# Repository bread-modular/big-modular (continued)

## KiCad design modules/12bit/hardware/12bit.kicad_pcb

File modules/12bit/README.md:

# 12bit — STM32G071 two-channel DAC voice (6HP)

modules/8bit moved from the ATtiny1616 to an **STM32G071C8T6**: its two 12-bit DAC channels
drive two outputs and the passive low-pass is gone (knob 3 is a plain knob). 6HP. (The S1
gate output was removed in S2. S3 adds a 3.0 V reference rail for the DACs, the ADC and the knobs.)

| Panel (top to bottom) | Circuit |
|---|---|
| **MIDI** in (TS) / **CV** in | 8bit MIDI V2 NPN front end, JP1 on the back (shipped open): `P` = protected (USART1 RX inverted in firmware), `D` = direct. CV: -5.9..+6.0 V -> 0..3.0 V (Zin 134k), BAT54SW clamp, MCP6001 follower into PA0; unpatched = 0 V |
| **P1**, **P2** / **MODE**, LED, **P3** | 50k linear RV09 dividers (on the +3V0 reference) into PA1 / PA6 / PA7. MODE: 8bit 6 x 6 x 7 mm THT switch (PB4) with the 8bit printed cap; 3 mm LED beside it on the same row (PB5, PWM) |
| **OUT 1**, **OUT 2** | DAC1_OUT1 / DAC1_OUT2 -> 1k/4.7n step smoothing (34 kHz) -> TL074 x3.7 around a 2.06 V offset -> ±4.8 V, DC coupled (audio, CV or LFO), 1k 0.5 W |

Power: Eurorack 10-pin (16-pin IDC fits) on B, upright at the right edge above OUT 2, ±12 V through series
Schottkys, +3V3 from an HT7533-1 for the MCU only. **+3V0** (S3): an LM4040 3.0 V shunt reference from
+12V_F for VREF+, the knobs, the output offset, the CV input and the MIDI pull-ups, so the MCU's supply
current no longer reaches the DAC reference (the first board buzzed with the knob ADC scan). SWD on a 1x5
header on B (1 3V3 sense, 2 SWDIO, 3 SWCLK, 4 GND, 5 NRST).

**Status: S3 schematic (ERC 0) + P3 placement + R3 2-layer hand routing (DRC 0, unconnected 0,
parity 0) + JLCPCB export in `jlcpcb/` (48 parts / 25 rows), 2026-11-19; not supplier-accepted, not built.
The first board (S2 / R2) is built and runs.** Firmware in `firmware/` (`clapsnare` drum voice, `osc3` test mixer, `humtest`); the same builds run on both boards. See `docs/research.md` for decisions and open items.

| Path | Contents |
|---|---|
| `hardware/` | KiCad project `12bit.kicad_{pro,sch,pcb}` (29 x 110 mm carrier, 2 layers, routed R3), pinned symbols/footprints/models |
| `panels/front-pcb/12bit-panel.kicad_{pro,pcb}` | 6HP FR4 front panel: NPTH only, silkscreen labels |
| `docs/research.md` | Brief, decisions, circuit, placement, open items |
| `docs/geometry.json` | Placement contract (panel frame) |
| `docs/12bit-schematic.pdf`, `docs/fit/` | Schematic PDF; native ERC/DRC JSON and renders |
| `docs/schematic-symbols.json`, `docs/sourcing-candidates.json` | Pinned-symbol provenance; dated live JLCPCB lookups |
| `tools/` | Generators and the shared-tool profile `kicad-project.json` |

Rebuild (from `modules/12bit`; the carrier is now routed, so `build_layout.py` refuses it; use `--panel-only` for the panel):

```sh
python3 -B tools/import_footprints.py   # one-time library import (pcbnew)
python3 -B tools/build_schematic.py     # schematic + pinned symbols, netlist asserted
python3 -B tools/build_layout.py        # THT placement + parked SMD + nets, UNROUTED; panel
(cd ../.. && python3 -B opt/kicad-tools/kicad_tools.py check --config modules/12bit/tools/kicad-project.json \
   --reports modules/12bit/research/check-NEW)
```

Read [`Code.md`](Code.md) before changing hardware.

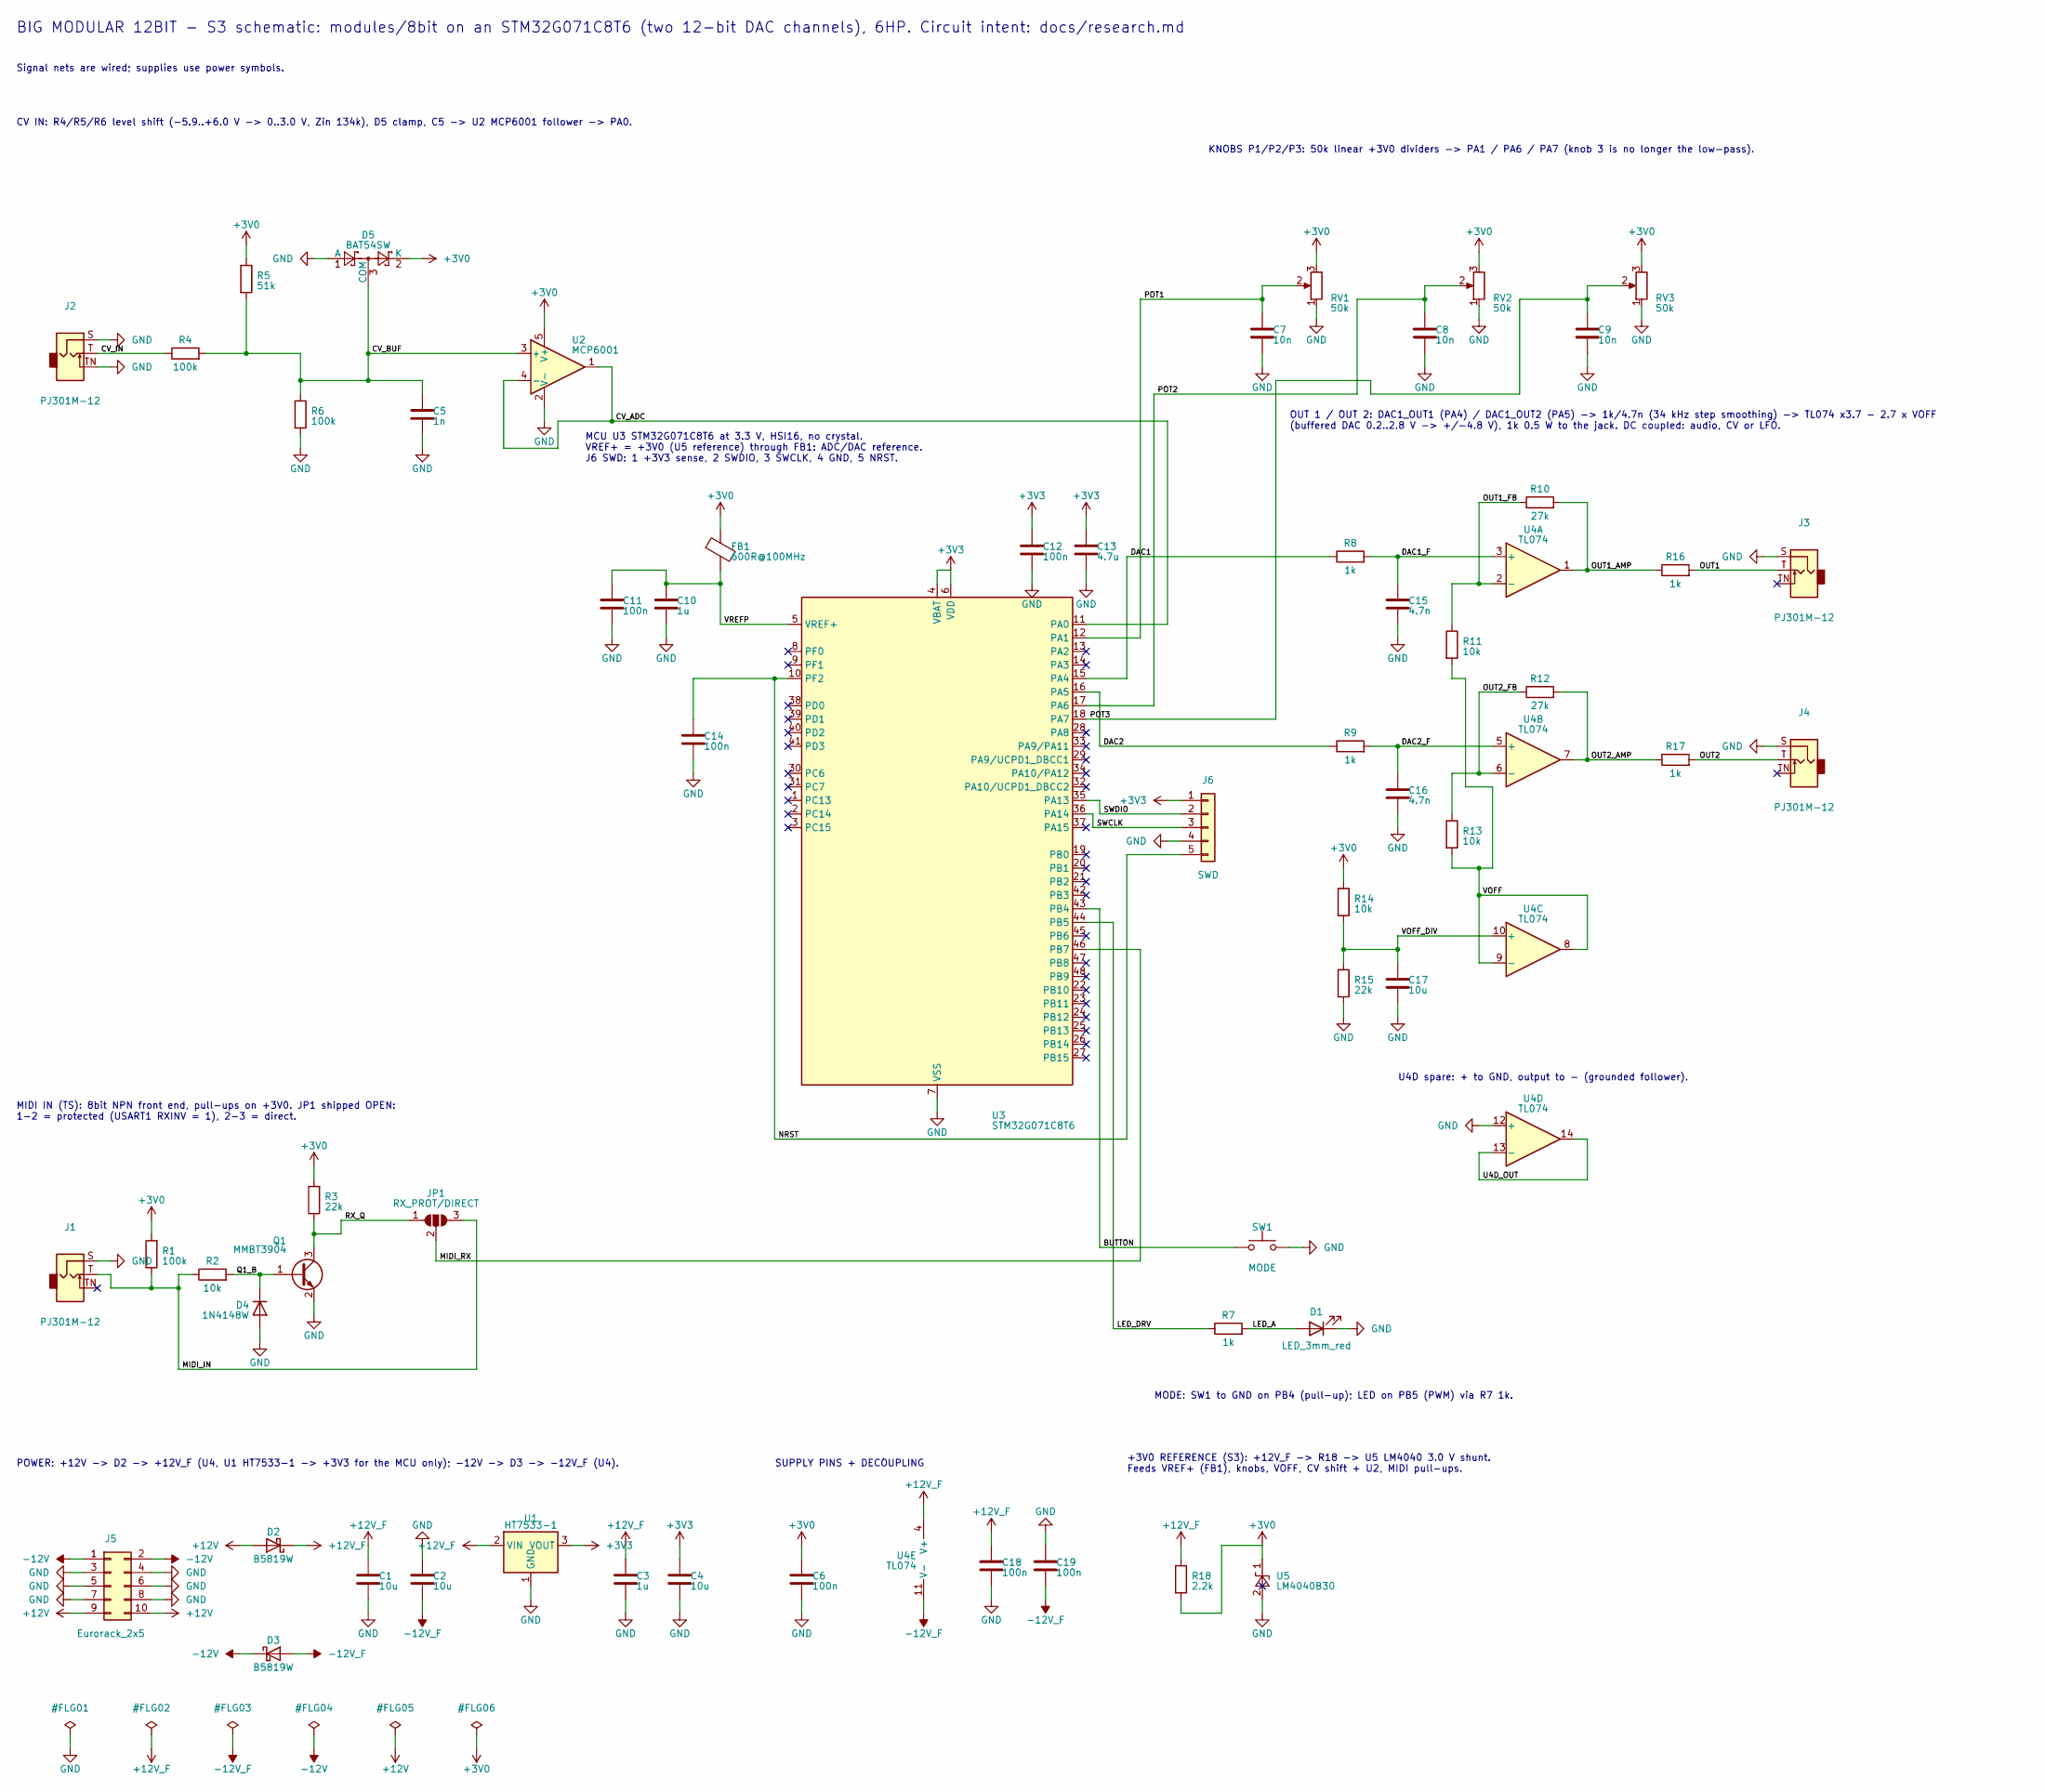
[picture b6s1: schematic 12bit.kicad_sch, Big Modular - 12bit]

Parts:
C1, C2, C4, C17: 10u; C_0805_2012Metric; Voltage 25V; MPN CL21A106KAYNNNE; LCSC C15850
C3, C10: 1u; C_0805_2012Metric; Voltage 50V; MPN CL21B105KBFNNNE; LCSC C28323
C5: 1n; C_0603_1608Metric; Voltage 50V; MPN CL10B102KB8NNNC; LCSC C1588
C6, C11, C12, C14, C18, C19: 100n; C_0603_1608Metric; Voltage 50V; MPN CC0603KRX7R9BB104; LCSC C14663
C7, C8, C9: 10n; C_0603_1608Metric; Voltage 50V; MPN 0603B103K500NT; LCSC C57112
C13: 4.7u; C_0603_1608Metric; Voltage 16V; MPN CL10A475KO8NNNC; LCSC C19666
C15, C16: 4.7n; C_0603_1608Metric; Voltage 50V; MPN 0603B472K500NT; LCSC C53987
D1: LED_3mm_red; LED_D3.0mm
D2, D3: B5819W; D_SOD-123; MPN B5819W SL; LCSC C8598
D4: 1N4148W; D_SOD-123; MPN 1N4148W; LCSC C81598
D5: BAT54SW; SOT-323_SC-70; MPN BAT54SWT1G; LCSC C78260
FB1: 600R@100MHz; L_0603_1608Metric; MPN GZ1608D601TF; LCSC C1002
J1, J2, J3, J4: PJ301M-12; Jack_3.5mm_QingPu_WQP-PJ301M-12_Vertical
J5: Eurorack_2x5; PinHeader_2x05_P2.54mm_Vertical
J6: SWD; PinHeader_1x05_P2.54mm_Vertical
JP1: RX_PROT/DIRECT; SolderJumper-3_P1.3mm_Open_RoundedPad1.0x1.5mm
Q1: MMBT3904; SOT-23; MPN MMBT3904(RANGE:100-300); LCSC C20526
R1, R4, R6: 100k; R_0603_1608Metric; MPN 0603WAF1003T5E; LCSC C25803
R2, R11, R13, R14: 10k; R_0603_1608Metric; MPN 0603WAF1002T5E; LCSC C25804
R3, R15: 22k; R_0603_1608Metric; MPN 0603WAF2202T5E; LCSC C31850
R5: 51k; R_0603_1608Metric; MPN 0603WAF5102T5E; LCSC C23196
R7, R8, R9: 1k; R_0603_1608Metric; MPN 0603WAF1001T5E; LCSC C21190
R10, R12: 27k; R_0603_1608Metric; MPN 0603WAF2702T5E; LCSC C22967
R16, R17: 1k; R_1206_3216Metric; MPN ESR18EZPF1001; LCSC C2074262
R18: 2.2k; R_0603_1608Metric; MPN 0603WAF2201T5E; LCSC C4190
RV1, RV2, RV3: 50k; Potentiometer_RV09
SW1: MODE; SW_PUSH_6mm_H7.3mm; MPN 6x6x7 mm THT tact switch, 4 pins (gener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
U1: HT7533-1; SOT-89-3; MPN HT7533-1; LCSC C14289
U2: MCP6001; SOT-23-5; MPN MCP6001T-E/OT; LCSC C29429
U3: STM32G071C8T6; LQFP-48_7x7mm_P0.5mm; MPN STM32G071C8T6; LCSC C529341
U4: TL074; SOIC-14_3.9x8.7mm_P1.27mm; MPN TL074CDR; LCSC C12594
U5: LM4040B30; SOT-23; MPN LM4040B30FTA; LCSC C460604

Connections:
+3V0: C6.1, D5.2 (K), FB1.1, R1.2, R3.2, R5.1, R14.1, R18.2, RV1.3, RV2.3, RV3.3, U2.5 (V+), U5.1 (K)
+3V3: C4.1, C12.1, C13.1, J6.1, U1.3 (VOUT), U3.4 (VBAT), U3.6 (VDD)
+12V: D2.2 (A), J5.9, J5.10
+12V_F: C1.1, C3.1, C18.1, D2.1 (K), R18.1, U1.2 (VIN), U4.4 (V+)
-12V: D3.1 (K), J5.1, J5.2
-12V_F: C2.2, C19.2, D3.2 (A), U4.11 (V-)
/BUTTON: SW1.1, U3.43 (PB4)
/CV_ADC: U2.1, U2.4 (-), U3.11 (PA0)
/CV_BUF: C5.1, D5.3 (COM), R4.2, R5.2, R6.1, U2.3 (+)
/CV_IN: J2.T, R4.1
/DAC1: R8.1, U3.15 (PA4)
/DAC1_F: C15.1, R8.2, U4.3 (+)
/DAC2: R9.1, U3.16 (PA5)
/DAC2_F: C16.1, R9.2, U4.5 (+)
/LED_A: D1.2 (A), R7.2
/LED_DRV: R7.1, U3.44 (PB5)
/MIDI_IN: J1.T, JP1.3 (B), R1.1, R2.1
/MIDI_RX: JP1.2 (C), U3.46 (PB7)
/NRST: C14.1, J6.5, U3.10 (PF2)
/OUT1: J3.T, R16.2
/OUT1_AMP: R10.2, R16.1, U4.1
/OUT1_FB: R10.1, R11.1, U4.2 (-)
/OUT2: J4.T, R17.2
/OUT2_AMP: R12.2, R17.1, U4.7
/OUT2_FB: R12.1, R13.1, U4.6 (-)
/POT1: C7.1, RV1.2, U3.12 (PA1)
/POT2: C8.1, RV2.2, U3.17 (PA6)
/POT3: C9.1, RV3.2, U3.18 (PA7)
/Q1_B: D4.1 (K), Q1.1 (B), R2.2
/RX_Q: JP1.1 (A), Q1.3 (C), R3.1
/SWCLK: J6.3, U3.36 (PA14)
/SWDIO: J6.2, U3.35 (PA13)
/U4D_OUT: U4.13 (-), U4.14
/VOFF: R11.2, R13.2, U4.8, U4.9 (-)
/VOFF_DIV: C17.1, R14.2, R15.1, U4.10 (+)
/VREFP: C10.1, C11.1, FB1.2, U3.5 (VREF+)
GND: C1.2, C2.1, C3.2, C4.2, C5.2, C6.2, C7.2, C8.2, C9.2, C10.2, C11.2, C12.2, C13.2, C14.2, C15.2, C16.2, C17.2, C18.2, C19.1, D1.1 (K), D4.2 (A), D5.1 (A), J1.S, J2.S, J2.TN, J3.S, J4.S, J5.3, J5.4, J5.5, J5.6, J5.7, J5.8, J6.4, Q1.2 (E), R6.2, R15.2, RV1.1, RV2.1, RV3.1, SW1.2, U1.1 (GND), U2.2 (V-), U3.7 (VSS), U4.12 (+), U5.2 (A)

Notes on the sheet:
+3V0 REFERENCE (S3): +12V_F -> R18 -> U5 LM4040 3.0 V shunt. Feeds VREF+ (FB1), knobs, VOFF, CV shift + U2, MIDI pull-ups.
CV IN: R4/R5/R6 level shift (-5.9..+6.0 V -> 0..3.0 V, Zin 134k), D5 clamp, C5 -> U2 MCP6001 follower -> PA0.
U4D spare: + to GND, output to - (grounded follower).
Signal nets are wired; supplies use power symbols.
SUPPLY PINS + DECOUPLING
MCU U3 STM32G071C8T6 at 3.3 V, HSI16, no crystal. VREF+ = +3V0 (U5 reference) through FB1: ADC/DAC reference. J6 SWD: 1 +3V3 sense, 2 SWDIO, 3 SWCLK, 4 GND, 5 NRST.
MODE: SW1 to GND on PB4 (pull-up); LED on PB5 (PWM) via R7 1k.
MIDI IN (TS): 8bit NPN front end, pull-ups on +3V0. JP1 shipped OPEN: 1-2 = protected (USART1 RXINV = 1), 2-3 = direct.
BIG MODULAR 12BIT - S3 schematic: modules/8bit on an STM32G071C8T6 (two 12-bit DAC channels), 6HP. Circuit intent: docs/research.md
KNOBS P1/P2/P3: 50k linear +3V0 dividers -> PA1 / PA6 / PA7 (knob 3 is no longer the low-pass).
OUT 1 / OUT 2: DAC1_OUT1 (PA4) / DAC1_OUT2 (PA5) -> 1k/4.7n (34 kHz step smoothing) -> TL074 x3.7 - 2.7 x VOFF (buffered DAC 0.2..2.8 V -> +/-4.8 V), 1k 0.5 W to the jack. DC coupled: audio, CV or LFO.
POWER: +12V -> D2 -> +12V_F (U4, U1 HT7533-1 -> +3V3 for the MCU only); -12V -> D3 -> -12V_F (U4).

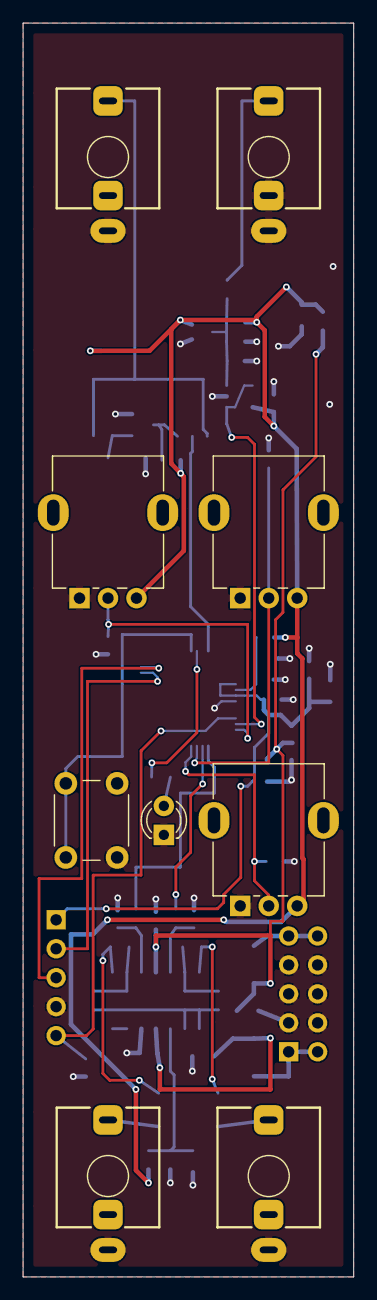
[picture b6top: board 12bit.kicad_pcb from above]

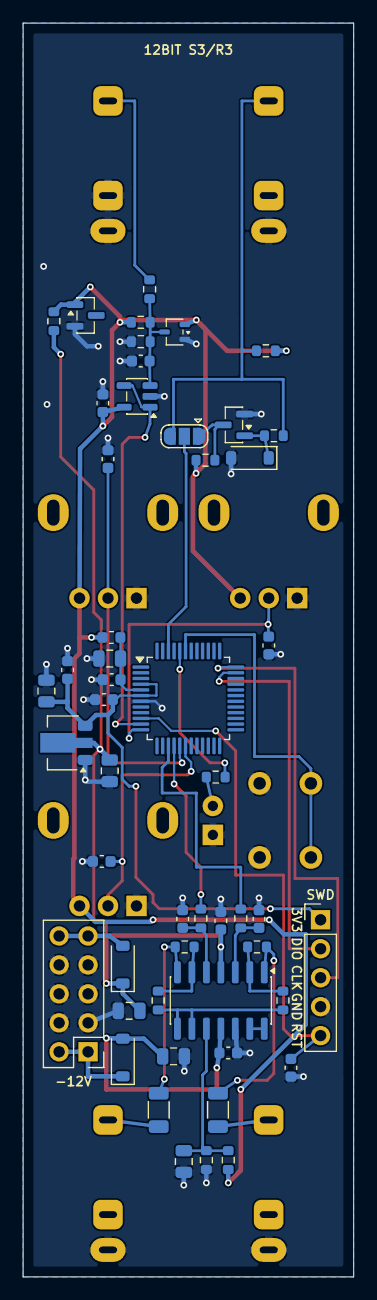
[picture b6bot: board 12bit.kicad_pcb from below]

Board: 2 copper layers, 29.0 x 110.0 mm, 60 parts (51 on the bottom side), 37 nets.

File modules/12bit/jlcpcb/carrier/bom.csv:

Comment,Designator,Footprint,LCSC Part #,Quantity,Manufacturer,MPN
10u,"C1, C2, C4, C17",C_0805_2012Metric,C15850,4,Samsung,CL21A106KAYNNNE
1u,"C3, C10",C_0805_2012Metric,C28323,2,Samsung,CL21B105KBFNNNE
1n,C5,C_0603_1608Metric,C1588,1,Samsung,CL10B102KB8NNNC
100n,"C6, C11, C12, C14, C18, C19",C_0603_1608Metric,C14663,6,YAGEO,CC0603KRX7R9BB104
10n,"C7, C8, C9",C_0603_1608Metric,C57112,3,FH (Guangdong Fenghua),0603B103K500NT
4.7u,C13,C_0603_1608Metric,C19666,1,Samsung,CL10A475KO8NNNC
4.7n,"C15, C16",C_0603_1608Metric,C53987,2,FH (Guangdong Fenghua),0603B472K500NT
B5819W,"D2, D3",D_SOD-123,C8598,2,CJ (Jiangsu Changjing),B5819W SL
1N4148W,D4,D_SOD-123,C81598,1,ST(Semtech),1N4148W
BAT54SW,D5,SOT-323_SC-70,C78260,1,onsemi,BAT54SWT1G
600R@100MHz,FB1,L_0603_1608Metric,C1002,1,Sunlord,GZ1608D601TF
MMBT3904,Q1,SOT-23,C20526,1,CJ (Jiangsu Changjing),MMBT3904(RANGE:100-300)
100k,"R1, R4, R6",R_0603_1608Metric,C25803,3,UNI-ROYAL,0603WAF1003T5E
10k,"R2, R11, R13, R14",R_0603_1608Metric,C25804,4,UNI-ROYAL,0603WAF1002T5E
22k,"R3, R15",R_0603_1608Metric,C31850,2,UNI-ROYAL,0603WAF2202T5E
51k,R5,R_0603_1608Metric,C23196,1,UNI-ROYAL,0603WAF5102T5E
1k,"R7, R8, R9",R_0603_1608Metric,C21190,3,UNI-ROYAL,0603WAF1001T5E
27k,"R10, R12",R_0603_1608Metric,C22967,2,UNI-ROYAL,0603WAF2702T5E
1k,"R16, R17",R_1206_3216Metric,C2074262,2,ROHM,ESR18EZPF1001
2.2k,R18,R_0603_1608Metric,C4190,1,UNI-ROYAL,0603WAF2201T5E
HT7533-1,U1,SOT-89-3,C14289,1,Holtek,HT7533-1
MCP6001,U2,SOT-23-5,C29429,1,Microchip,MCP6001T-E/OT
STM32G071C8T6,U3,LQFP-48_7x7mm_P0.5mm,C529341,1,STMicroelectronics,STM32G071C8T6
TL074,U4,SOIC-14_3.9x8.7mm_P1.27mm,C12594,1,Texas Instruments,TL074CDR
LM4040B30,U5,SOT-23,C460604,1,Diodes Incorporated,LM4040B30FTA

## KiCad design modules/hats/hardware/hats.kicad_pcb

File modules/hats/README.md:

# HATS

6HP Eurorack hi-hat: Bread Modular NOISE (blue noise, NOISE TONE / BLUE TONE) feeding the
Bread Modular HIHAT (CUTOFF, vactrol VCA, closed-hat DECAY), driven by shared MIDI.
NOISE IN replaces the internal noise through protected jack-contact detection.
Outputs: AUDIO (nominal ~10 Vpp) and HAT CV (intended 0..5 V) with ENV LED.

**S4 schematic (2026-11-08):** one STM32G071C8T6 runs both Bread Modular firmwares; CUTOFF is
read by the ADC and played on a second vactrol by PWM, so CUTOFF and NOISE TONE can be recorded
(REC button + LED at the bottom). **R4** carrier routed by hand for S4 (4 layers, all SMD on the
back, ERC 0 / unconnected 0 / parity 0), **P5** panel with the REC button and LED holes, JLCPCB
re-exported. The new vactrol U11 under NOISE TONE / BLUE TONE adds stacking DRC items that still
need your approval. The STM32 firmware is in `firmware/` (compiled and host-tested, not run on hardware yet).
**R5** (2026-11-09) = R4 copper with fab-review silk fixes: SWD pin legend on J11, larger vactrol
assembly notes clear of the pot pads, `-12V` beside the power header, `HATS R5` board text.
**R6** (2026-11-09) = fab fixes: the MCU's supply, reference and reset caps (C6, C25, C26) moved to
their pins with a local re-route, heat-spreading copper on both sides of the 3.3 V regulator tab
(U1), the U11 vactrol stacking findings approved and excluded like U7's, `HATS R6` board text.

**S5 / R7** (2026-11-19) = the modules/12bit reference fix on this board: an LM4040 3.0 V reference (U12, fed by R52
from +12 V) now supplies the DAC/ADC reference pin and the two MCU-read knobs, instead of the 3.3 V MCU supply. Two new
parts, hand-routed, `HATS R7` board text, JLCPCB re-exported (97 parts / 35 BOM rows). The firmware reads the knobs on a
fixed 100 kHz timer, as the 12bit fix. Not built or measured.

**S3 schematic / R3 routed four-layer carrier / P4 panel.** Recording functionality,
button, LED and associated circuitry have been removed. Pot row spacing is **34 mm**
(previously 24 mm); all pots upright, with the vactrol on the back under CUTOFF (as on
LOW). Copper setback is **1 mm**; all assembled SMD is on the back.

JLCPCB files: `jlcpcb/` (re-exported from S5/R7/P5, 2026-11-19). See `jlcpcb/README.md`, `docs/research.md` and
`docs/noise-in-protection.md`. Exported, not supplier-accepted or bench-validated.
Until S5 the DAC reference was the +3V3 rail; S5 moves it to +3V0 (user, 2026-11-19).

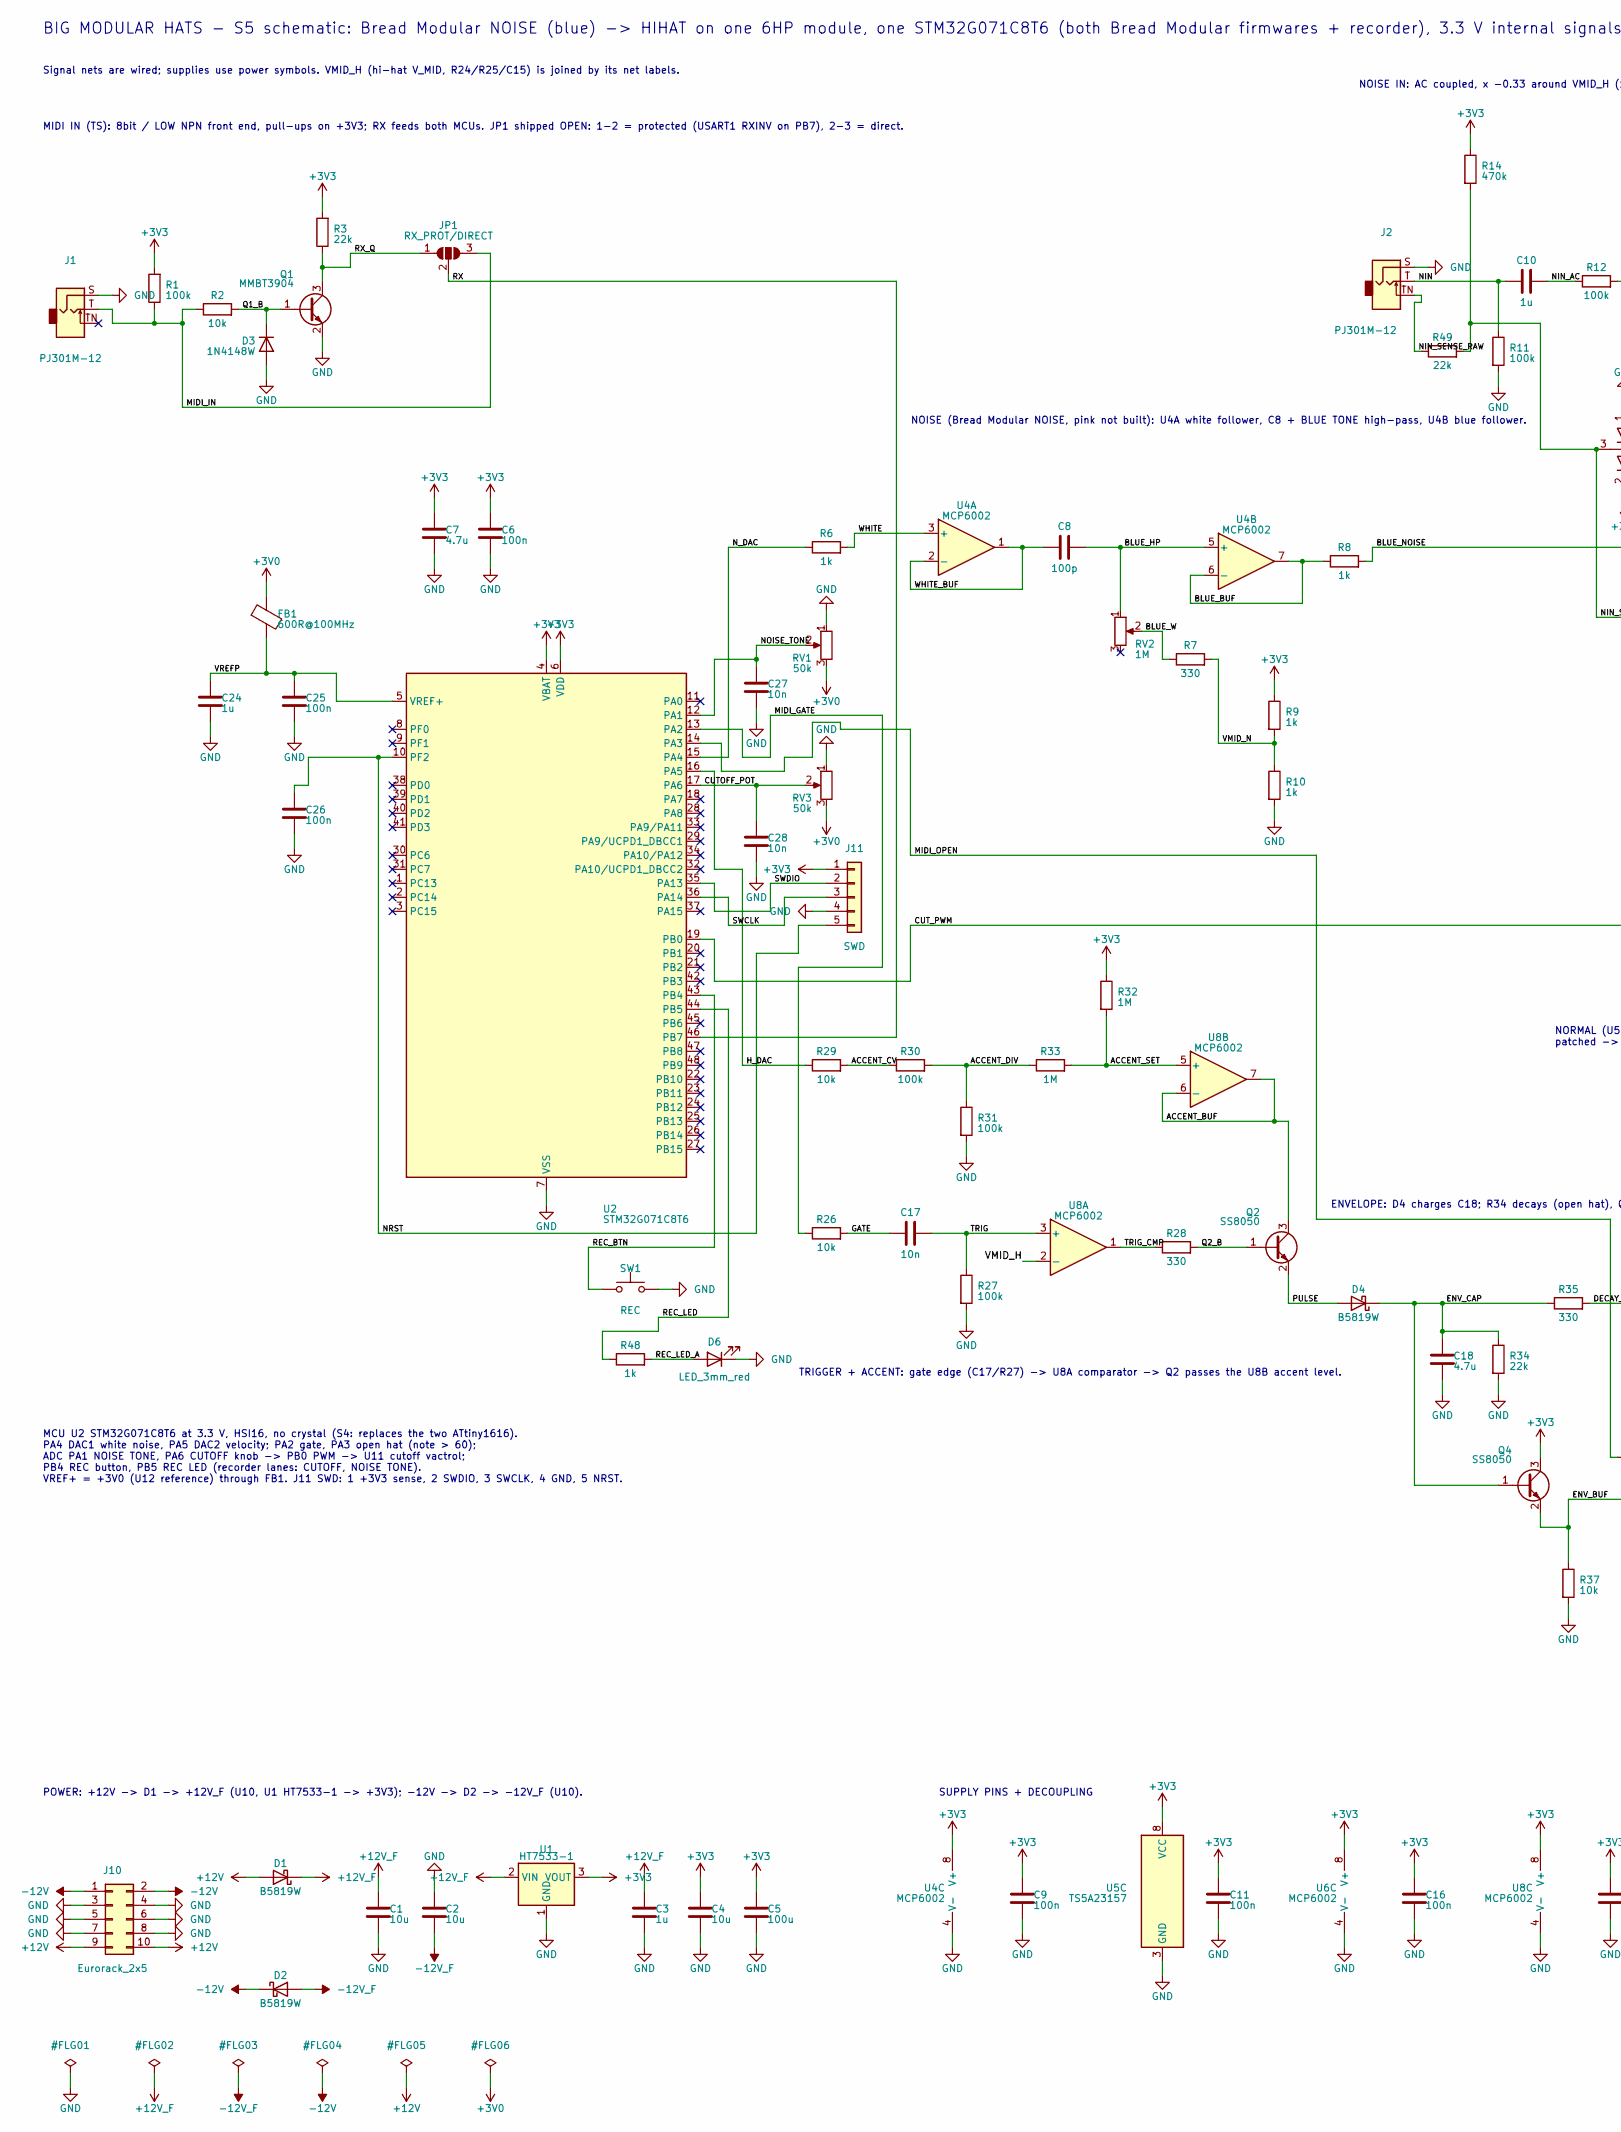
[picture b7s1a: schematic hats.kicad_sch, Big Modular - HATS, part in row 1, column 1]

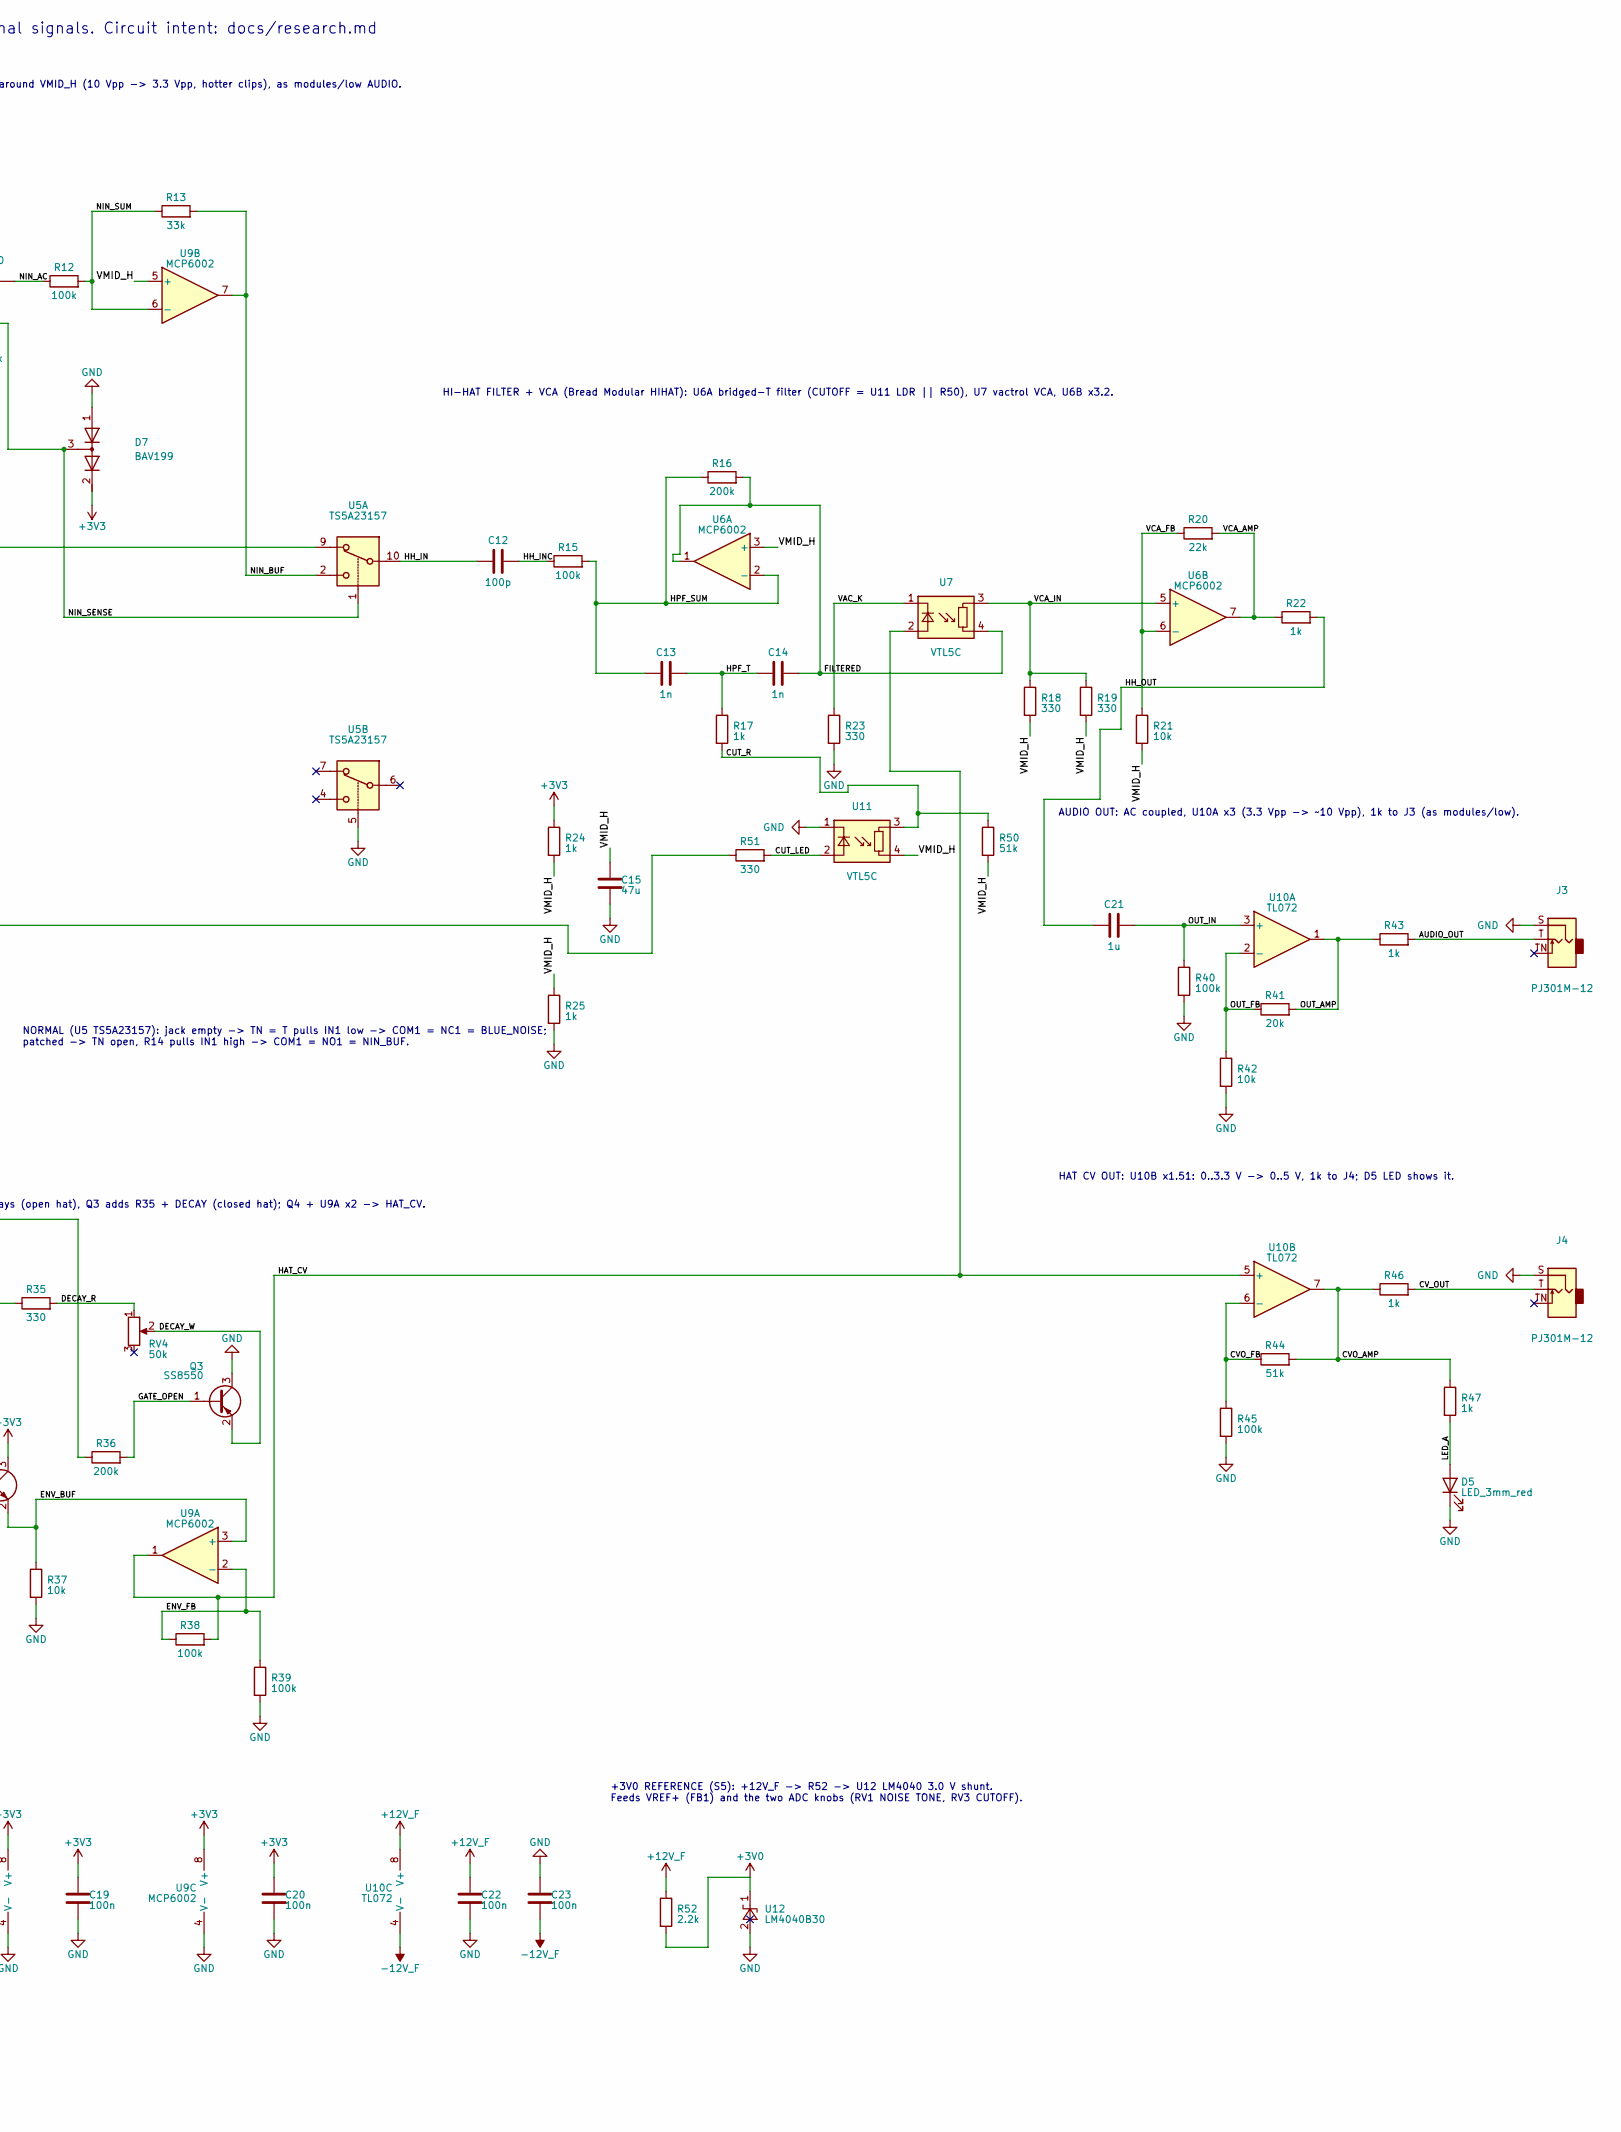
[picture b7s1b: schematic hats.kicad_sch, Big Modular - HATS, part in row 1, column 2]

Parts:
C1, C2, C4: 10u; C_0805_2012Metric; Voltage 25V; MPN CL21A106KAYNNNE; LCSC C15850
C3, C10, C24: 1u; C_0805_2012Metric; Voltage 50V; MPN CL21B105KBFNNNE; LCSC C28323
C5: 100u; C_1206_3216Metric; Voltage 6.3V; MPN CL31A107MQHNNNE; LCSC C15008
C6, C9, C11, C16, C19, C20, C22, C23, C25, C26: 100n; C_0603_1608Metric; Voltage 50V; MPN CC0603KRX7R9BB104; LCSC C14663
C7, C18: 4.7u; C_0603_1608Metric; Voltage 16V; MPN CL10A475KO8NNNC; LCSC C19666
C8, C12: 100p; C_0603_1608Metric; Voltage 50V; MPN CL10C101JB8NNNC; LCSC C14858
C13, C14: 1n; C_0603_1608Metric; Voltage 50V; MPN CL10B102KB8NNNC; LCSC C1588
C15: 47u; C_0805_2012Metric; Voltage 6.3V; MPN CL21A476MQYNNNE; LCSC C16780
C17, C27, C28: 10n; C_0603_1608Metric; Voltage 50V; MPN 0603B103K500NT; LCSC C57112
C21: 1u; C_0805_2012Metric; Voltage 25V; MPN CL21B105KBFNNNE; LCSC C28323
D1, D2, D4: B5819W; D_SOD-123; MPN B5819W SL; LCSC C8598
D3: 1N4148W; D_SOD-123; MPN 1N4148W; LCSC C81598
D5, D6: LED_3mm_red; LED_D3.0mm
D7: BAV199; SOT-23; MPN BAV199,215; LCSC C40919
FB1: 600R@100MHz; L_0603_1608Metric; MPN GZ1608D601TF; LCSC C1002
J1, J2, J3, J4: PJ301M-12; Jack_3.5mm_QingPu_WQP-PJ301M-12_Vertical
J10: Eurorack_2x5; PinHeader_2x05_P2.54mm_Vertical
J11: SWD; PinHeader_1x05_P2.54mm_Vertical
JP1: RX_PROT/DIRECT; SolderJumper-3_P1.3mm_Open_RoundedPad1.0x1.5mm
Q1: MMBT3904; SOT-23; MPN MMBT3904(RANGE:100-300); LCSC C20526
Q2, Q4: SS8050; SOT-23; MPN SS8050; LCSC C431710
Q3: SS8550; SOT-23; MPN SS8550; LCSC C364314
R1, R11, R12, R15, R27, R30, R31, R38, R39, R40, R45: 100k; R_0603_1608Metric; MPN 0603WAF1003T5E; LCSC C25803
R2, R21, R26, R29, R37, R42: 10k; R_0603_1608Metric; MPN 0603WAF1002T5E; LCSC C25804
R3, R20, R34, R49: 22k; R_0603_1608Metric; MPN 0603WAF2202T5E; LCSC C31850
R6, R8, R9, R10, R17, R22, R24, R25, R47, R48: 1k; R_0603_1608Metric; MPN 0603WAF1001T5E; LCSC C21190
R7, R18, R19, R23, R28, R35, R51: 330; R_0603_1608Metric; MPN 0603WAF3300T5E; LCSC C23138
R13: 33k; R_0603_1608Metric; MPN 0603WAF3302T5E; LCSC C4216
R14: 470k; R_0603_1608Metric; MPN 0603WAF4703T5E; LCSC C23178
R16, R36: 200k; R_0603_1608Metric; MPN 0603WAF2003T5E; LCSC C25811
R32, R33: 1M; R_0603_1608Metric; MPN 0603WAF1004T5E; LCSC C22935
R41: 20k; R_0603_1608Metric; MPN 0603WAF2002T5E; LCSC C4184
R43, R46: 1k; R_1206_3216Metric; MPN ESR18EZPF1001; LCSC C2074262
R44, R50: 51k; R_0603_1608Metric; MPN 0603WAF5102T5E; LCSC C23196
R52: 2.2k; R_0603_1608Metric; MPN 0603WAF2201T5E; LCSC C4190
RV1, RV3, RV4: 50k; Potentiometer_RV09
RV2: 1M; Potentiometer_RV09
SW1: REC; SW_PUSH_6mm_H7.3mm; MPN 6x6x7 mm THT tact switch, 4 pins (gener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
U1: HT7533-1; SOT-89-3; MPN HT7533-1; LCSC C14289
U2: STM32G071C8T6; LQFP-48_7x7mm_P0.5mm; MPN STM32G071C8T6; LCSC C529341
U4, U6, U8, U9: MCP6002; SOIC-8_3.9x4.9mm_P1.27mm; MPN MCP6002T-I/SN; LCSC C7377
U5: TS5A23157; TSSOP-10_3x3mm_P0.5mm; MPN TS5A23157DGSR; LCSC C11133
U7, U11: VTL5C
U10: TL072; SOIC-8_3.9x4.9mm_P1.27mm; MPN TL072CDT; LCSC C6961
U12: LM4040B30; SOT-23; MPN LM4040B30FTA; LCSC C460604

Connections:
+3V0: FB1.1, R52.2, RV1.3, RV3.3, U12.1 (K)
+3V3: C4.1, C5.1, C6.1, C7.1, C9.1, C11.1, C16.1, C19.1, C20.1, D7.2 (K), J11.1, Q4.3 (C), R1.2, R3.2, R9.1, R14.1, R24.1, R32.1, U1.3 (VOUT), U2.4 (VBAT), U2.6 (VDD), U4.8 (V+), U5.8 (VCC), U6.8 (V+), U8.8 (V+), U9.8 (V+)
+12V: D1.2 (A), J10.9, J10.10
+12V_F: C1.1, C3.1, C22.1, D1.1 (K), R52.1, U1.2 (VIN), U10.8 (V+)
-12V: D2.1 (K), J10.1, J10.2
-12V_F: C2.2, C23.2, D2.2 (A), U10.4 (V-)
/ACCENT_BUF: Q2.3 (C), U8.6 (-), U8.7
/ACCENT_CV: R29.2, R30.1
/ACCENT_DIV: R30.2, R31.1, R33.1
/ACCENT_SET: R32.2, R33.2, U8.5 (+)
/AUDIO_OUT: J3.T, R43.2
/BLUE_BUF: R8.1, U4.6 (-), U4.7
/BLUE_HP: C8.2, RV2.1, U4.5 (+)
/BLUE_NOISE: R8.2, U5.9
/BLUE_W: R7.1, RV2.2
/CUTOFF_POT: C28.1, RV3.2, U2.17 (PA6)
/CUT_LED: R51.2, U11.2 (+)
/CUT_PWM: R51.1, U2.19 (PB0)
/CUT_R: R17.2, R50.1, U11.3
/CVO_AMP: R44.2, R46.1, R47.1, U10.7
/CVO_FB: R44.1, R45.1, U10.6 (-)
/CV_OUT: J4.T, R46.2
/DECAY_R: R35.2, RV4.1
/DECAY_W: Q3.2 (E), RV4.2
/ENV_BUF: Q4.2 (E), R37.1, U9.3 (+)
/ENV_CAP: C18.1, D4.1 (K), Q4.1 (B), R34.1, R35.1
/ENV_FB: R38.1, R39.1, U9.2 (-)
/FILTERED: C14.2, R16.2, U6.1, U7.4
/GATE: C17.1, R26.2
/GATE_OPEN: Q3.1 (B), R36.2
/HAT_CV: R38.2, U7.2 (+), U9.1, U10.5 (+)
/HH_IN: C12.1, U5.10
/HH_INC: C12.2, R15.1
/HH_OUT: C21.1, R22.2
/HPF_SUM: C13.1, R15.2, R16.1, U6.2 (-)
/HPF_T: C13.2, C14.1, R17.1
/H_DAC: R29.1, U2.16 (PA5)
/LED_A: D5.2 (A), R47.2
/MIDI_GATE: R26.1, U2.13 (PA2)
/MIDI_IN: J1.T, JP1.3 (B), R1.1, R2.1
/MIDI_OPEN: R36.1, U2.14 (PA3)
/NIN: C10.1, J2.T, R11.1
/NIN_AC: C10.2, R12.1
/NIN_BUF: R13.2, U5.2, U9.7
/NIN_SENSE: D7.3 (common), R14.2, R49.2, U5.1
/NIN_SENSE_RAW: J2.TN, R49.1
/NIN_SUM: R12.2, R13.1, U9.6 (-)
/NOISE_TONE: C27.1, RV1.2, U2.12 (PA1)
/NRST: C26.1, J11.5, U2.10 (PF2)
/N_DAC: R6.1, U2.15 (PA4)
/OUT_AMP: R41.2, R43.1, U10.1
/OUT_FB: R41.1, R42.1, U10.2 (-)
/OUT_IN: C21.2, R40.1, U10.3 (+)
/PULSE: D4.2 (A), Q2.2 (E)
/Q1_B: D3.1 (K), Q1.1 (B), R2.2
/Q2_B: Q2.1 (B), R28.2
/REC_BTN: SW1.1, U2.43 (PB4)
/REC_LED: R48.1, U2.44 (PB5)
/REC_LED_A: D6.2 (A), R48.2
/RX: JP1.2 (C), U2.46 (PB7)
/RX_Q: JP1.1 (A), Q1.3 (C), R3.1
/SWCLK: J11.3, U2.36 (PA14)
/SWDIO: J11.2, U2.35 (PA13)
/TRIG: C17.2, R27.1, U8.3 (+)
/TRIG_CMP: R28.1, U8.1
/VAC_K: R23.1, U7.1 (-)
/VCA_AMP: R20.2, R22.1, U6.7
/VCA_FB: R20.1, R21.1, U6.6 (-)
/VCA_IN: R18.1, R19.1, U6.5 (+), U7.3
/VMID_H: C15.1, R18.2, R19.2, R21.2, R24.2, R25.1, R50.2, U6.3 (+), U8.2 (-), U9.5 (+), U11.4
/VMID_N: R7.2, R9.2, R10.1
/VREFP: C24.1, C25.1, FB1.2, U2.5 (VREF+)
/WHITE: R6.2, U4.3 (+)
/WHITE_BUF: C8.1, U4.1, U4.2 (-)
GND: C1.2, C2.1, C3.2, C4.2, C5.2, C6.2, C7.2, C9.2, C11.2, C15.2, C16.2, C18.2, C19.2, C20.2, C22.2, C23.1, C24.2, C25.2, C26.2, C27.2, C28.2, D3.2 (A), D5.1 (K), D6.1 (K), D7.1 (A), J1.S, J2.S, J3.S, J4.S, J10.3, J10.4, J10.5, J10.6, J10.7, J10.8, J11.4, Q1.2 (E), Q3.3 (C), R10.2, R11.2, R23.2, R25.2, R27.2, R31.2, R34.2, R37.2, R39.2, R40.2, R42.2, R45.2, RV1.1, RV3.1, SW1.2, U1.1 (GND), U2.7 (VSS), U4.4 (V-), U5.3 (GND), U5.5, U6.4 (V-), U8.4 (V-), U9.4 (V-), U11.1 (-), U12.2 (A)

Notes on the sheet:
SUPPLY PINS + DECOUPLING
HI-HAT FILTER + VCA (Bread Modular HIHAT): U6A bridged-T filter (CUTOFF = U11 LDR || R50), U7 vactrol VCA, U6B x3.2.
Signal nets are wired; supplies use power symbols. VMID_H (hi-hat V_MID, R24/R25/C15) is joined by its net labels.
BIG MODULAR HATS - S5 schematic: Bread Modular NOISE (blue) -> HIHAT on one 6HP module, one STM32G071C8T6 (both Bread Modular firmwares + recorder), 3.3 V internal signals. Circuit intent: docs/research.md
AUDIO OUT: AC coupled, U10A x3 (3.3 Vpp -> ~10 Vpp), 1k to J3 (as modules/low).
ENVELOPE: D4 charges C18; R34 decays (open hat), Q3 adds R35 + DECAY (closed hat); Q4 + U9A x2 -> HAT_CV.
HAT CV OUT: U10B x1.51: 0..3.3 V -> 0..5 V, 1k to J4; D5 LED shows it.
TRIGGER + ACCENT: gate edge (C17/R27) -> U8A comparator -> Q2 passes the U8B accent level.
MCU U2 STM32G071C8T6 at 3.3 V, HSI16, no crystal (S4: replaces the two ATtiny1616). PA4 DAC1 white noise, PA5 DAC2 velocity; PA2 gate, PA3 open hat (note > 60); ADC PA1 NOISE TONE, PA6 CUTOFF knob -> PB0 PWM -> U11 cutoff vactrol; PB4 REC button, PB5 REC LED (recorder lanes: CUTOFF, NOISE TONE). VR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
NOISE IN: AC coupled, x -0.33 around VMID_H (10 Vpp -> 3.3 Vpp, hotter clips), as modules/low AUDIO.
POWER: +12V -> D1 -> +12V_F (U10, U1 HT7533-1 -> +3V3); -12V -> D2 -> -12V_F (U10).
NOISE (Bread Modular NOISE, pink not built): U4A white follower, C8 + BLUE TONE high-pass, U4B blue follower.
NORMAL (U5 TS5A23157): jack empty -> TN = T pulls IN1 low -> COM1 = NC1 = BLUE_NOISE; patched -> TN open, R14 pulls IN1 high -> COM1 = NO1 = NIN_BUF.
+3V0 REFERENCE (S5): +12V_F -> R52 -> U12 LM4040 3.0 V shunt. Feeds VREF+ (FB1) and the two ADC knobs (RV1 NOISE TONE, RV3 CUTOFF).
MIDI IN (TS): 8bit / LOW NPN front end, pull-ups on +3V3; RX feeds both MCUs. JP1 shipped OPEN: 1-2 = protected (USART1 RXINV on PB7), 2-3 = direct.
